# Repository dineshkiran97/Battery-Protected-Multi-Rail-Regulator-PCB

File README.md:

# Battery-Protected Multi-Rail Regulator PCB

KiCad project for a battery-powered linear regulator board that generates two
regulated rails (5V and 3.3V) from a single-cell battery input, with reverse-polarity
protection and a power-on indicator.

## Overview

- **Input:** Single-cell battery via a 2-pin JST PH connector (J1)
- **Protection:** Series Schottky diode (D1, 1N5820) blocks reverse-polarity connection
- **Outputs:** Two independently regulated rails
  - 3.3V via U1 (LDL1117S33R)
  - 5.0V via U2 (LDL1117S50R)
- **Indicator:** Power-on LED (D2, LTST-C171KGKT) with current-limiting resistor (R1, 255Ω)
- **Breakout:** 4-pin header (J3) exposing BAT / 5V / 3.3V / GND for downstream boards
- **Layout:** 2-layer PCB, fully routed (0 unrouted nets), DRC clean (0 errors)

## Schematic

| Ref | Part | Function |
|---|---|---|
| U1 | LDL1117S33R | 3.3V fixed LDO regulator (SOT-23-5) |
| U2 | LDL1117S50R | 5.0V fixed LDO regulator (SOT-23-5) |
| D1 | 1N5820 | Schottky diode, reverse-polarity protection |
| D2 | LTST-C171KGKT | Power-on indicator LED |
| R1 | 255Ω | LED current-limiting resistor |
| C1, C2 | 1µF (0805) | Input decoupling caps |
| C3, C4 | 4.7µF (0805) | Output decoupling caps |
| J1 | B2B-PH-K-S | 2-pin battery input connector |
| J2 | PC712A | Auxiliary connector/switch |
| J3 | Conn_01x04 | 4-pin breakout header (BAT/5V/3.3V/GND) |

Full details in [`hardware/BOM.csv`](hardware/BOM.csv).

## Repository structure

```
.
├── README.md
├── LICENSE
├── .gitignore
├── hardware/
│   ├── VLO.kicad_pro
│   ├── VLO.kicad_sch
│   ├── VLO.kicad_pcb
│   └── BOM.csv
├── production/
│   ├── gerbers/
│   ├── BOM.csv
│   └── pos.csv
└── images/
    ├── schematic.png
    ├── pcb-layout.png
    └── pcb-3d.png
```

Drop your `.kicad_pro` / `.kicad_sch` / `.kicad_pcb` files into `hardware/`, and export
Gerbers + a top-view PCB screenshot into `production/` and `images/` respectively.

## Design notes

- D1 sits in series between the battery connector and the BAT rail, so a reversed
  battery simply doesn't power the board instead of damaging U1/U2.
- Input caps are 1µF and output caps are 4.7µF per regulator, per the LDL1117
  datasheet's minimum stability requirements.
- DRC was run with **0 errors**; a small number of warnings remain (silkscreen
  clearance on densely packed 0805 footprints) and are cosmetic, not functional.

## Status

- [x] Schematic capture
- [x] Footprint assignment
- [x] 2-layer routing (0 unrouted nets)
- [x] DRC (0 errors)
- [ ] Gerbers exported / fab-ready

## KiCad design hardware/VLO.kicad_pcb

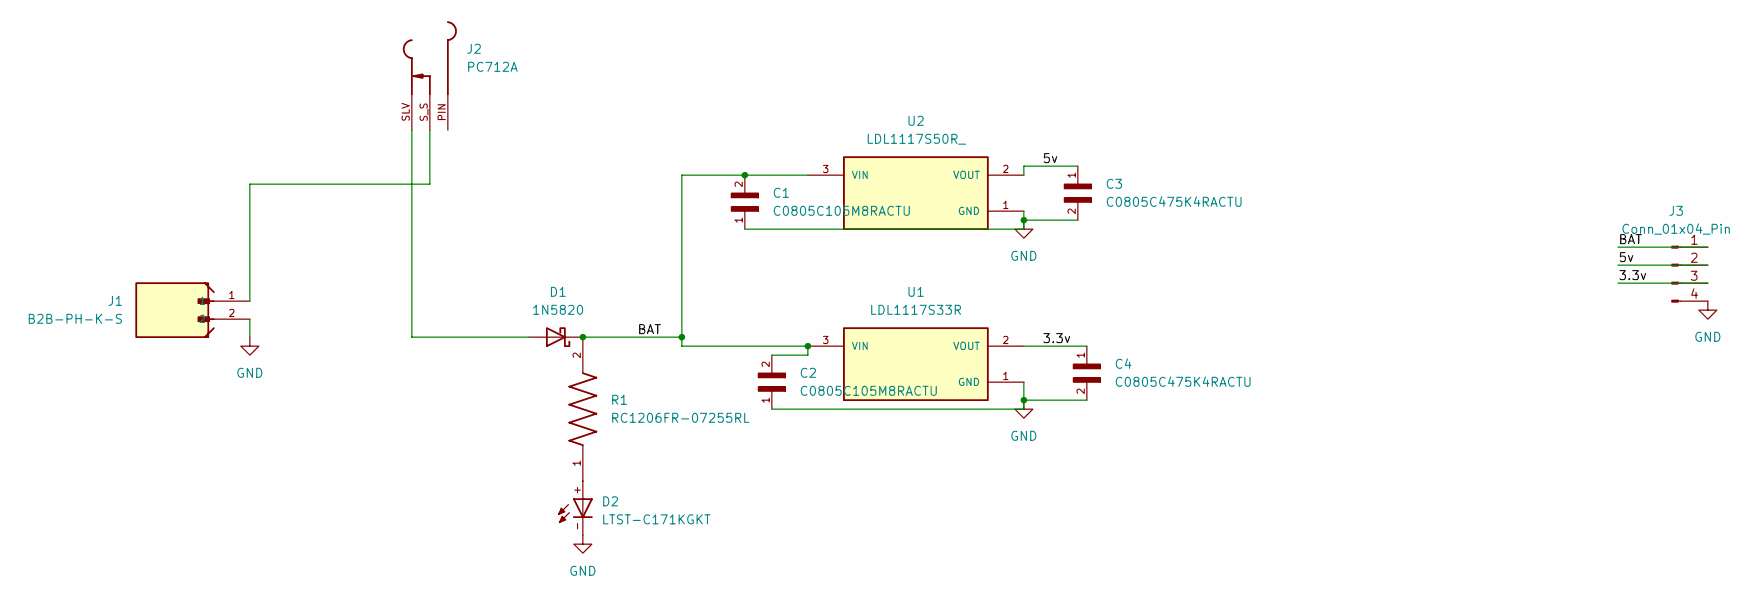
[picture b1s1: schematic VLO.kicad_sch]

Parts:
C1, C2: C0805C105M8RACTU; CAPC2012X100N
C3, C4: C0805C475K4RACTU; CAPC2012X88N
D1: 1N5820; D_DO-201AD_P15.24mm_Horizontal
D2: LTST-C171KGKT; DIOC200X125X110
J1: B2B-PH-K-S; JST_B2B-PH-K-S
J2: PC712A; SWITCHCRAFT_PC712A; PARTREV G; DigiKey_Part_Number SC1050-ND
J3: Conn_01x04_Pin; PinHeader_1x04_P2.54mm_Vertical
R1: RC1206FR-07255RL; RESC3116X65N
U1: LDL1117S33R; SOT230P700X180-4N; PARTREV 7
U2: LDL1117S50R_; SOT230P700X180-4N; PARTREV 7

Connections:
/3.3v: C4.1, J3.3, U1.2 (VOUT), U1.4 (VOUT)
/5v: C3.1, J3.2, U2.2 (VOUT), U2.4 (VOUT)
/BAT: C1.2, C2.2, D1.1 (K), J3.1, R1.2, U1.3 (VIN), U2.3 (VIN)
GND: C1.1, C2.1, C3.2, C4.2, D2.-, J1.2, J3.4, U1.1 (GND), U2.1 (GND)
unnamed: D1.2 (A), J2.SLV
unnamed: D2.+, R1.1
unnamed: J1.1, J2.S_S

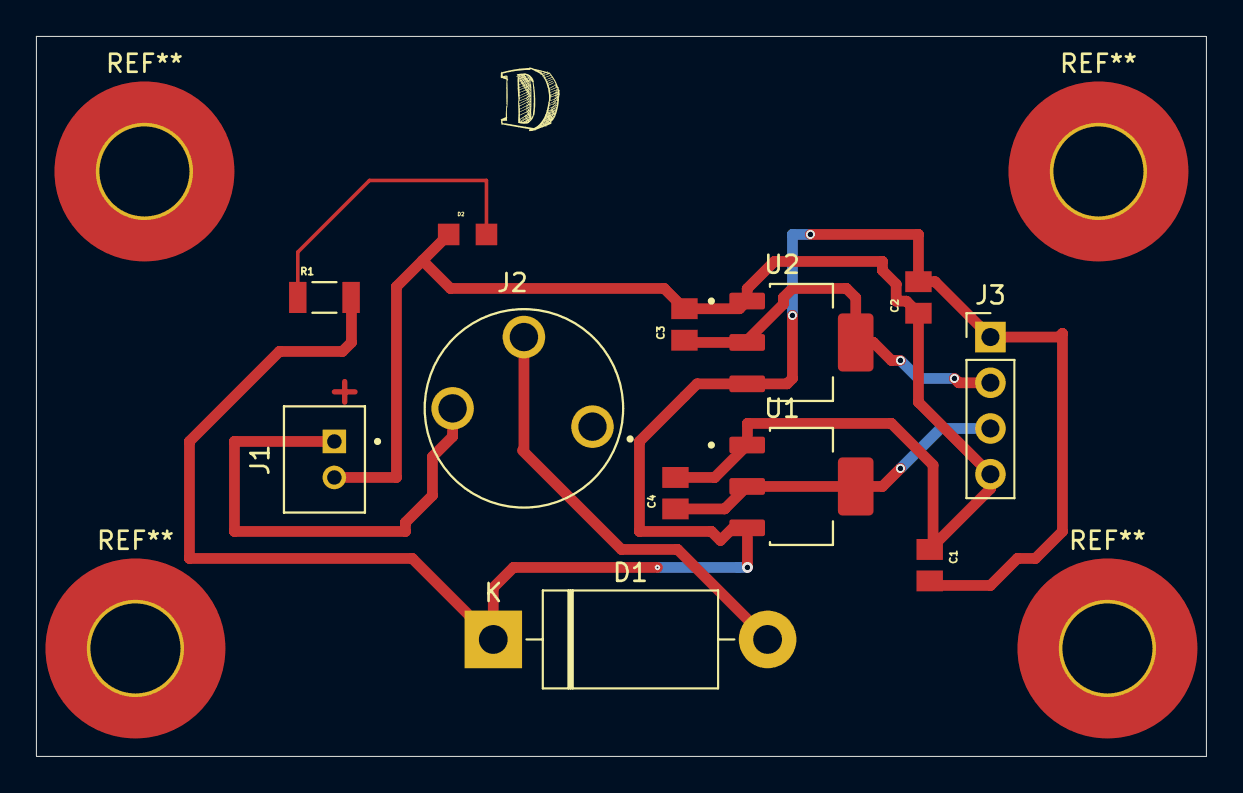
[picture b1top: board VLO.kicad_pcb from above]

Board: 2 copper layers, 65.0 x 40.0 mm, 12 parts (0 on the bottom side), 7 nets.
